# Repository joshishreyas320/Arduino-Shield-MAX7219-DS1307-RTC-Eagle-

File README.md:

# Arduino Shield – MAX7219 7-Segment Display + DS1307 RTC

> Eagle CAD PCB Design | 2-Layer Shield | MAX7219 + DS1307

---

## Project Description
An Arduino shield PCB designed using **Eagle CAD** that integrates a **MAX7219CNG** SPI LED driver and a **DS1307** I2C real-time clock. The shield drives a **4-digit 7-segment display (NFD-5641AS)** and shows real-time clock data. A **CR1220 backup battery** and **32.768kHz crystal** maintain RTC timekeeping during power-off. Standard Arduino R3 headers allow direct plug-in to Arduino UNO or Mega.

**Short Description (≤350 chars):**
> Arduino shield PCB using MAX7219 SPI 7-segment driver + DS1307 I2C RTC. Displays real-time clock data on 4-digit display. CR1220 battery backup, 32.768kHz crystal. Designed in Eagle CAD.

---

## Key Components

| Component | Description |
|-----------|-------------|
| **MAX7219CNG** | SPI-controlled 8-digit LED display driver |
| **DS1307** | I2C real-time clock IC |
| **NFD-5641AS** | 4-digit 7-segment common-cathode display |
| **CR1220 (SMT)** | 3V backup battery for RTC |
| **32.768kHz Crystal** | Precise RTC time reference |
| **Arduino R3 Headers** | Standard shield interface (ICSP + pins) |
| **Pull-up Resistors (4.7kΩ)** | I2C SDA/SCL pull-ups |
| **Decoupling Caps (0.1µF)** | Supply noise filtering |

---

## Design Features
- MAX7219 drives 4-digit 7-segment display via 3-wire SPI
- DS1307 provides seconds/minutes/hours/date over I2C (TWI)
- CR1220 backup battery keeps RTC running when Arduino is off
- 32.768kHz crystal ensures accurate 1-second RTC tick
- Standard Arduino R3 form factor – direct plug-in, no wiring needed
- Both SPI and I2C interfaces used simultaneously on Arduino

---

## Signal Flow
```
Arduino UNO / Mega – Host MCU
       ↓ SPI (MOSI / SCK / SS)
  MAX7219CNG – LED Driver
       ↓
  NFD-5641AS – 4-Digit 7-Segment Display
       ↓ I2C (SDA / SCL)
  DS1307 RTC – Real-Time Clock
       ↑
  32.768kHz Crystal ← RTC Clock Reference
  CR1220 Battery ← RTC Backup Power
```

---

## Files Included
- a_Arduino Shield MAX7219.sch – Eagle Schematic
- a_Arduino Shield MAX7219.brd – Eagle PCB Layout
- Gerber_files_a_Arduino Shield MAX7219_2026-05-20.zip – Gerber files

---

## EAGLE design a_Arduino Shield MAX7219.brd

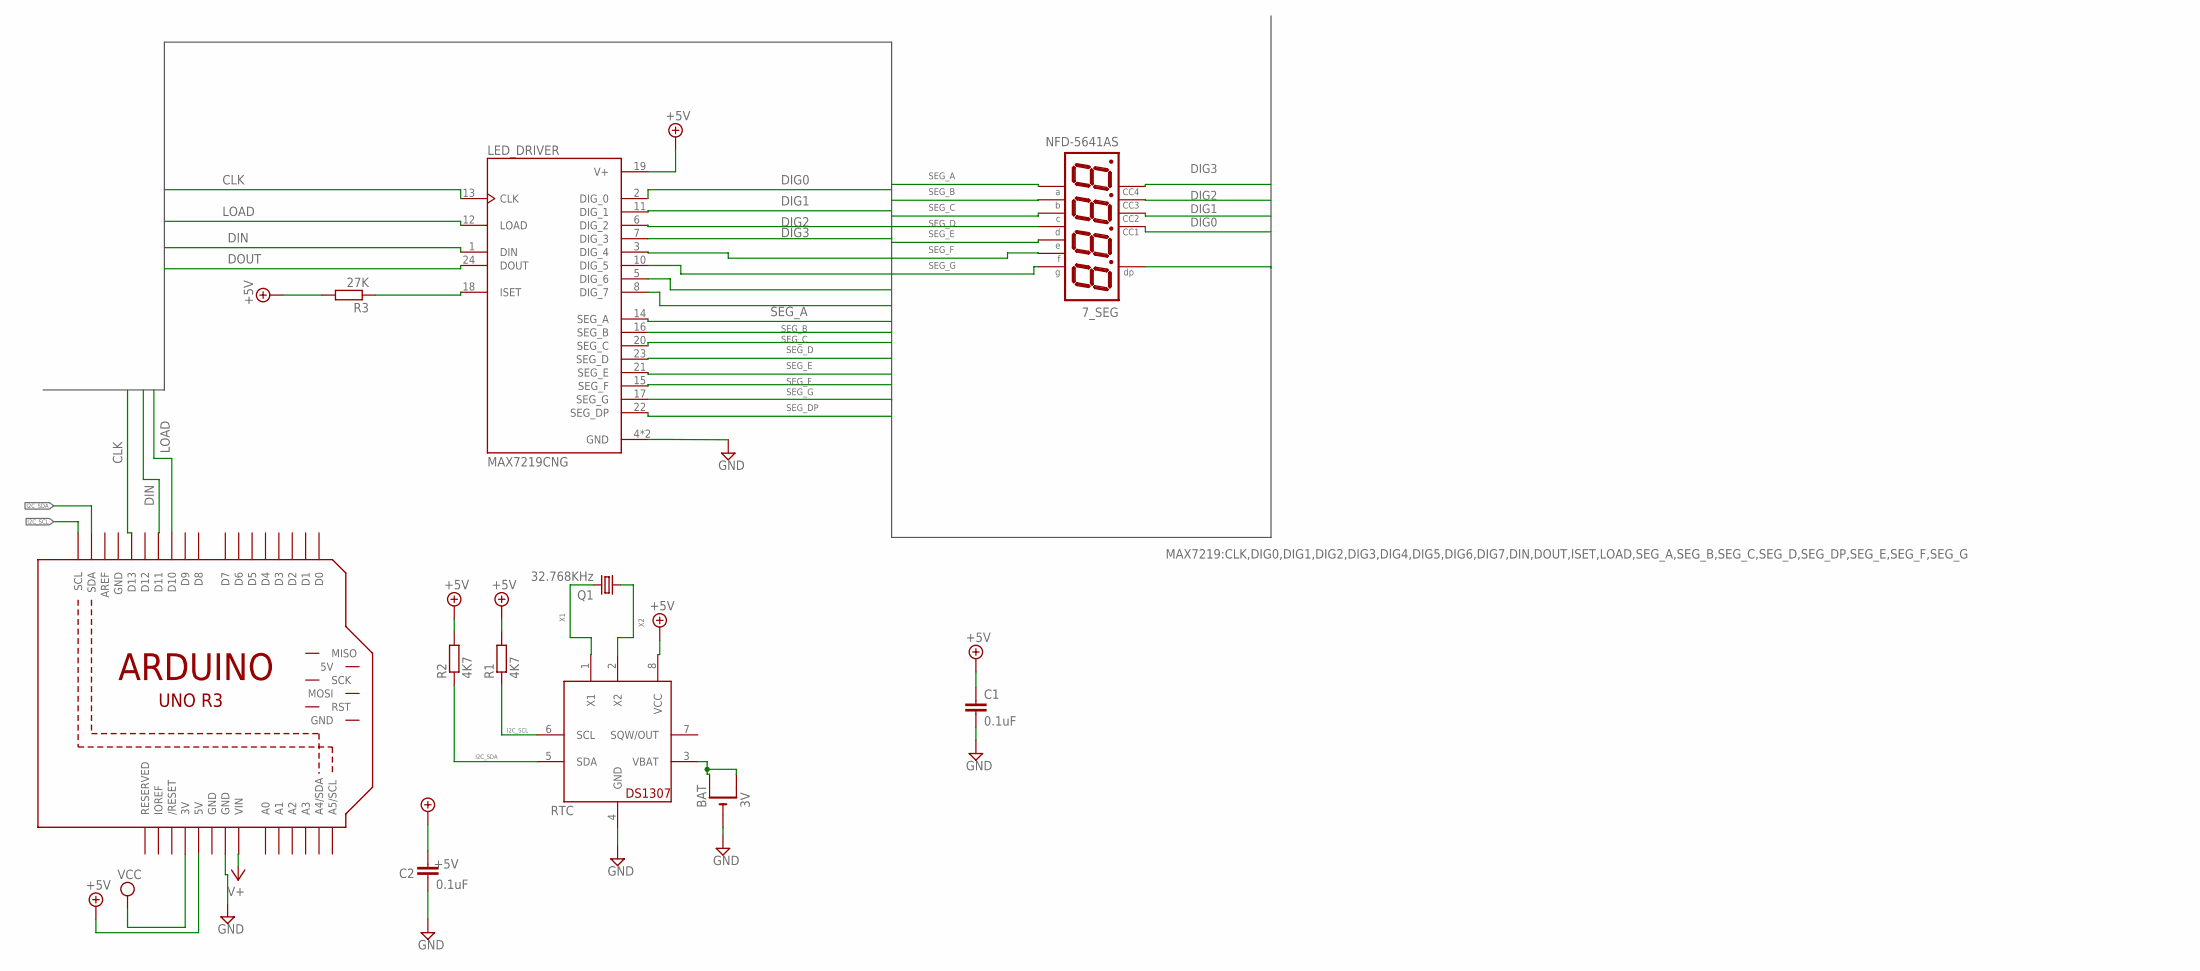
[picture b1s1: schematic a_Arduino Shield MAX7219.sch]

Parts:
7_SEG: NFD-5641AS; NFD-5641
BAT: 3V; CR1220-SMD
C1, C2: 0.1uF; C050-025X075
LED_DRIVER: MAX7219CNG; DIP762W47P254L3054H457Q24B
M1: ARDUINO_R3_ICSP; ARDUINOR3_ICSP
Q1: 32.768KHz; TC38H
R1, R2: 4K7; M1206
R3: 27K; M1206
RTC: DS1307; DIL08

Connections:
+5V: C1.1, C2.1, LED_DRIVER.19 (V+), M1.5V, R1.2, R2.2, R3.2, RTC.8 (VCC)
CLK: LED_DRIVER.13 (CLK), M1.D13
DIG0: 7_SEG.P$12, LED_DRIVER.2 (DIG_0)
DIG1: 7_SEG.P$9, LED_DRIVER.11 (DIG_1)
DIG2: 7_SEG.P$8, LED_DRIVER.6 (DIG_2)
DIG3: 7_SEG.P$6, LED_DRIVER.7 (DIG_3)
DIG4: LED_DRIVER.3 (DIG_4)
DIG5: LED_DRIVER.10 (DIG_5)
DIG6: LED_DRIVER.5 (DIG_6)
DIG7: LED_DRIVER.8 (DIG_7)
DIN: LED_DRIVER.1 (DIN), M1.D11
DOUT: LED_DRIVER.24 (DOUT)
GND: BAT.-, C1.2, C2.2, LED_DRIVER.4 (GND), LED_DRIVER.9 (GND), M1.GND, M1.GND@1 (GND), M1.GND@3 (GND), RTC.4 (GND)
I2C_SCL: M1.SCL, R1.1, RTC.6 (SCL)
I2C_SDA: M1.SDA, R2.1, RTC.5 (SDA)
LOAD: LED_DRIVER.12 (LOAD), M1.D10
unnamed: LED_DRIVER.18 (ISET), R3.1
unnamed: BAT.+$1 (+), BAT.+$2 (+1), RTC.3 (VBAT)
SEG_A: 7_SEG.P$11, LED_DRIVER.14 (SEG_A)
SEG_B: 7_SEG.P$7, LED_DRIVER.16 (SEG_B)
SEG_C: 7_SEG.P$4, LED_DRIVER.20 (SEG_C)
SEG_D: 7_SEG.P$2, LED_DRIVER.23 (SEG_D)
SEG_DP: 7_SEG.P$3, LED_DRIVER.22 (SEG_DP)
SEG_E: 7_SEG.P$1, LED_DRIVER.21 (SEG_E)
SEG_F: 7_SEG.P$10, LED_DRIVER.15 (SEG_F)
SEG_G: 7_SEG.P$5, LED_DRIVER.17 (SEG_G)
V+: M1.VIN
VCC: M1.3V
X1: Q1.2, RTC.1 (X1)
X2: Q1.1, RTC.2 (X2)

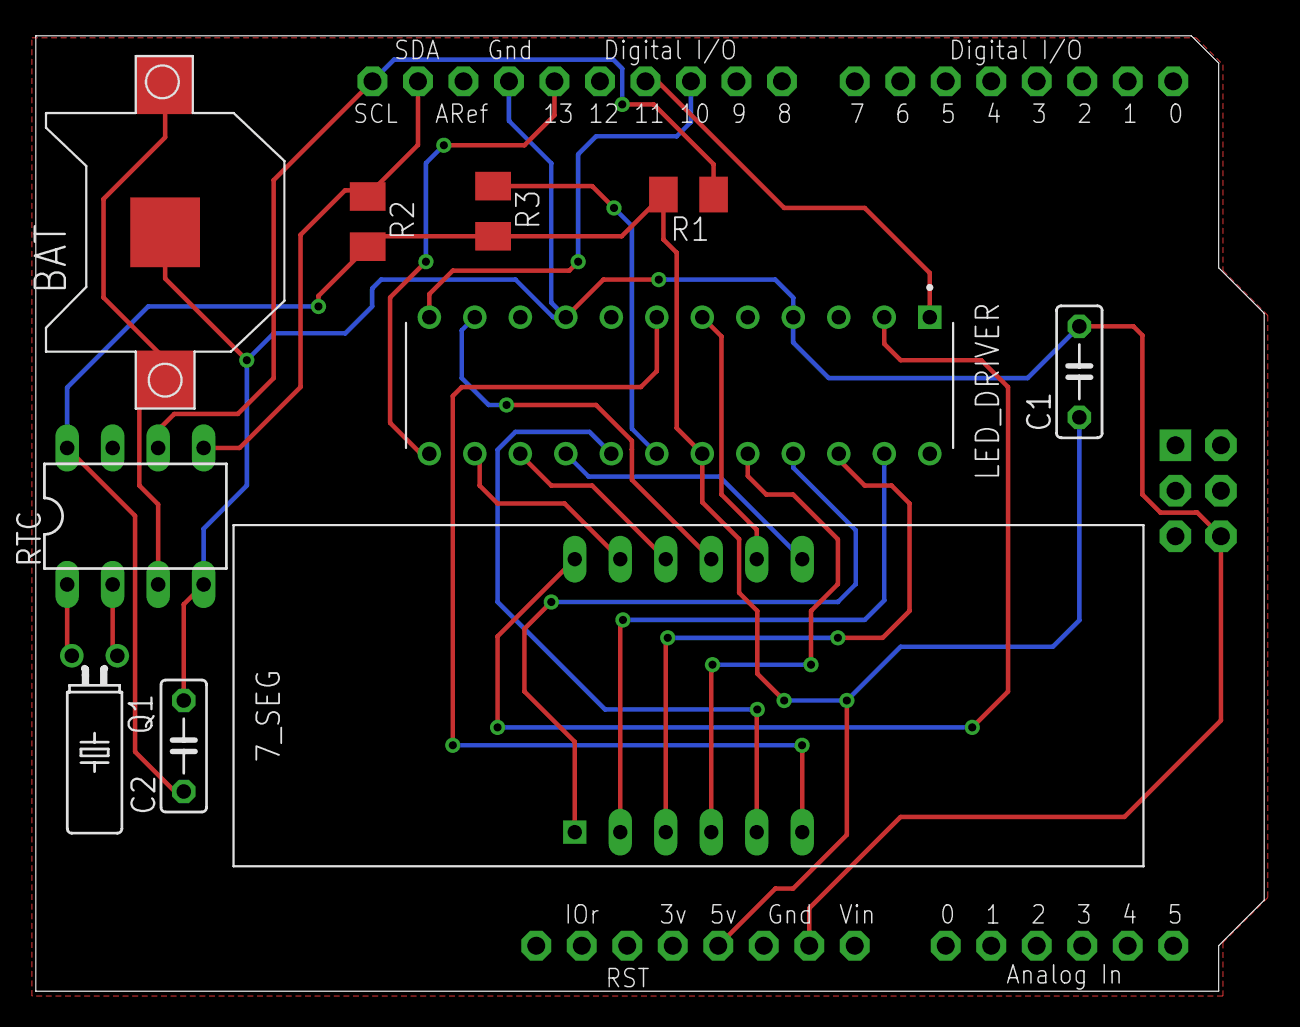
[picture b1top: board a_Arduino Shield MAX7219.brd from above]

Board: 2 copper layers, 68.6 x 53.3 mm, 11 parts (0 on the bottom side), 23 nets.

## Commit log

2026-06-06 Revise README with detailed project information
    Updated project description and key components in README.
